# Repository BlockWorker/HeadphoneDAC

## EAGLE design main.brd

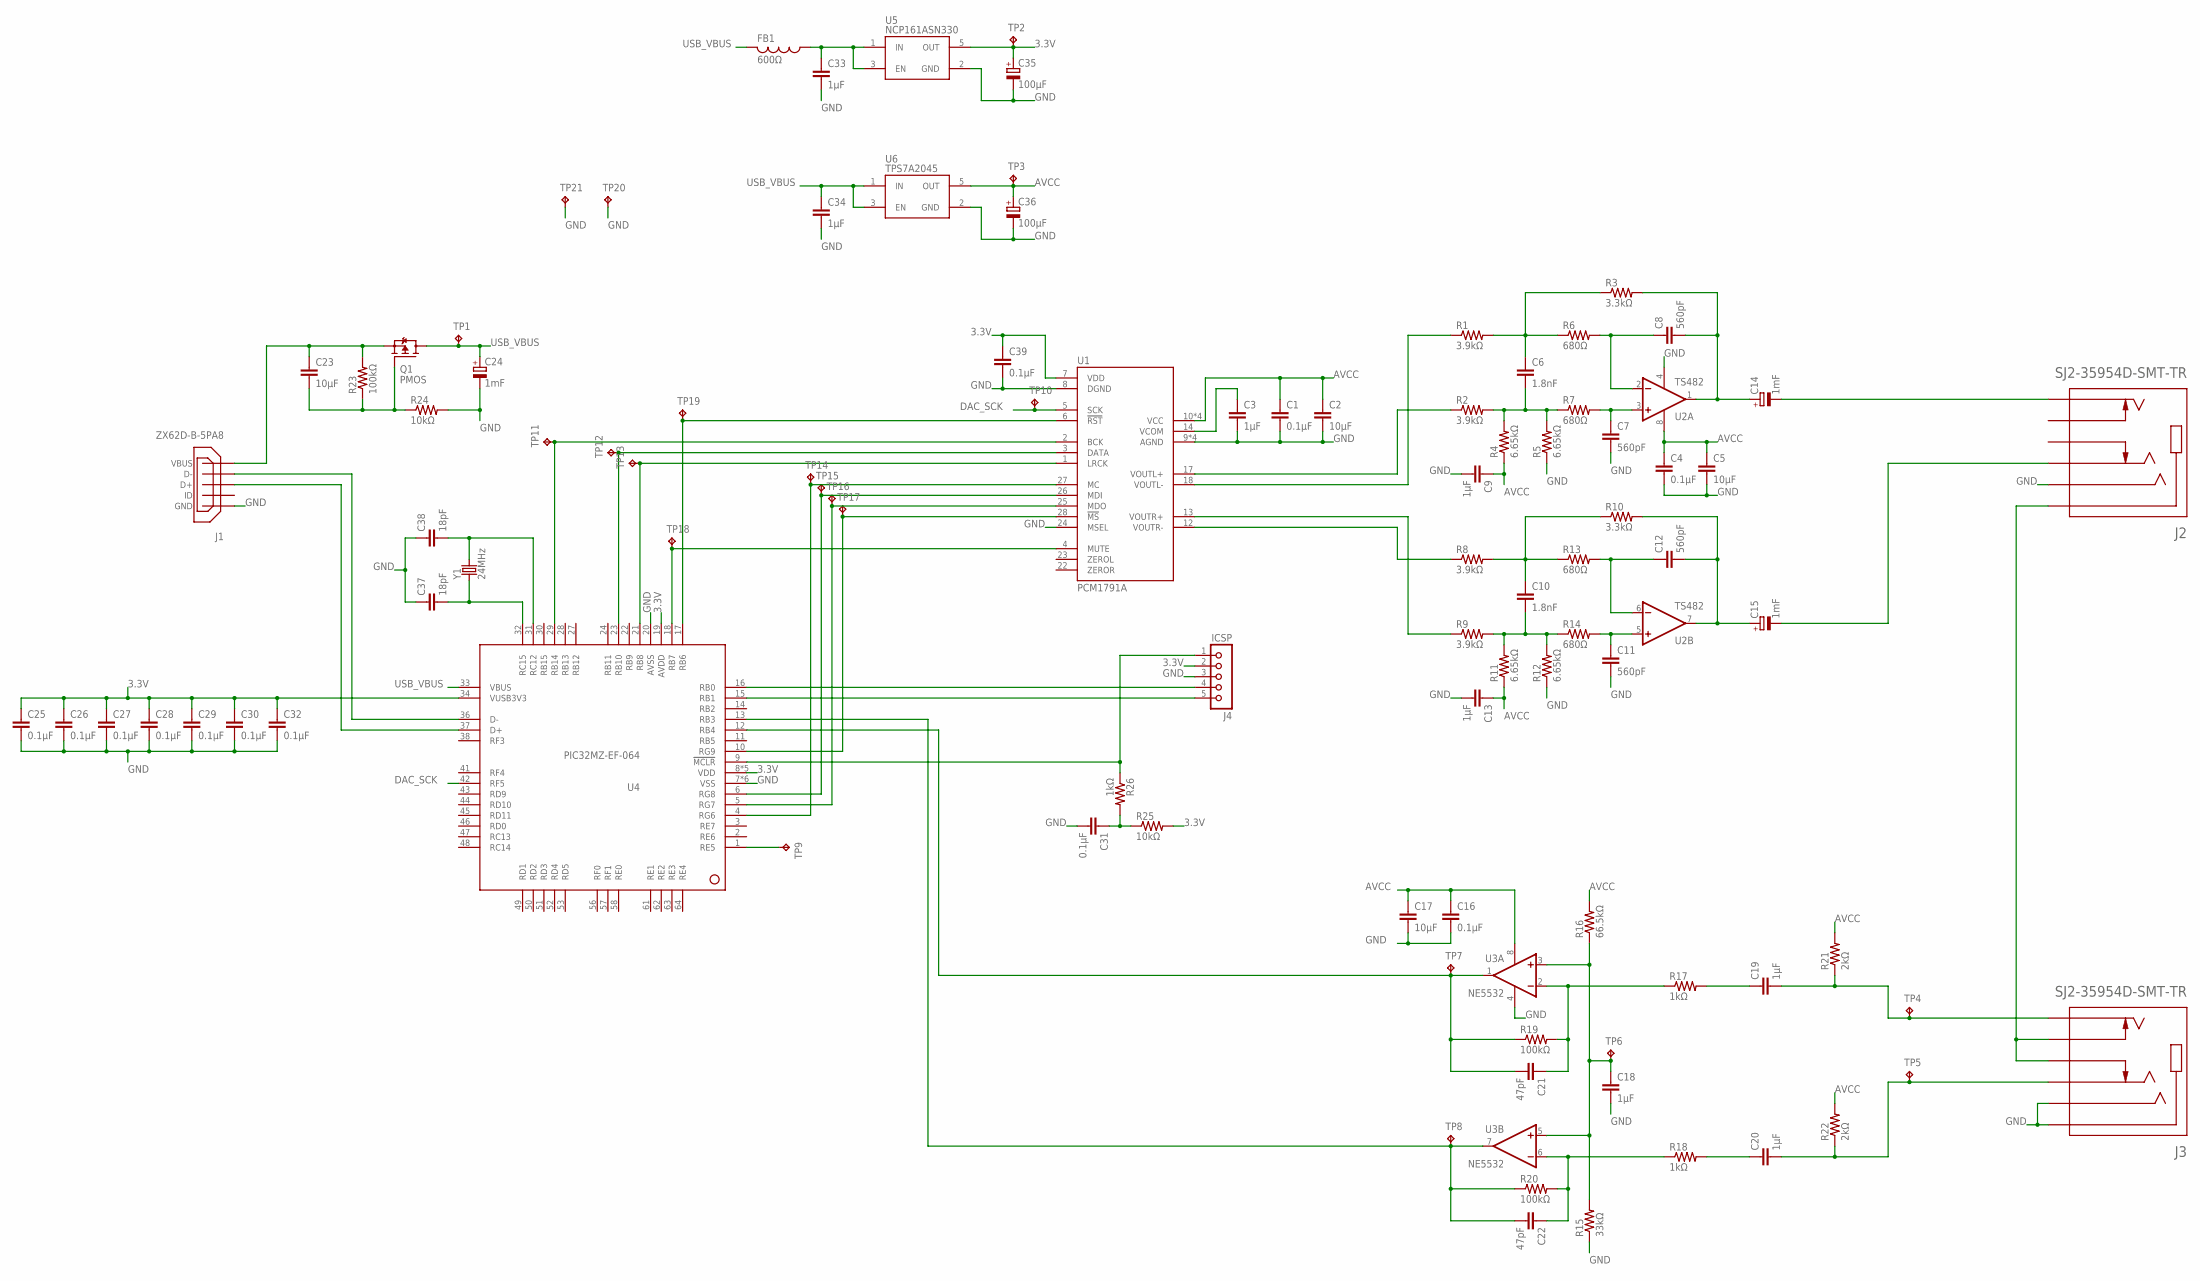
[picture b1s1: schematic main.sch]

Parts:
C1, C4, C16, C25, C26, C27, C28, C29, C30, C31, C32, C39: 0.1µF; C0603
C2, C5, C17, C23: 10µF; C0805
C3, C9, C13, C18, C33, C34: 1µF; C0805
C6, C10: 1.8nF; C0603
C7, C8, C11, C12: 560pF; C0603
C14, C15, C24: 1mF; E3,5-8-16-HORZ
C19, C20: 1µF; C050-050X075
C21, C22: 47pF; C050-045X075
C35, C36: 100µF; PANASONIC_D
C37, C38: 18pF; C0603
FB1: 600Ω; C0603
J1: ZX62D-B-5PA8
J2, J3: SJ2-35954D-SMT-TR; CUI_SJ2-35954D-SMT-TR
J4: ICSP; 5PIN-1.27
Q1: PMOS; SOT23
R1, R2, R8, R9: 3.9kΩ; R0603
R3, R10: 3.3kΩ; R0603
R4, R5, R11, R12: 6.65kΩ; R0603
R6, R7, R13, R14: 680Ω; R0603
R15: 33kΩ; R0603
R16: 66.5kΩ; R0603
R17, R18, R26: 1kΩ; R0603
R19, R20, R23: 100kΩ; R0603
R21, R22: 2kΩ; R0603
R24, R25: 10kΩ; R0603
TP1, TP2, TP3, TP4, TP5, TP6, TP7, TP8, TP9, TP10, TP11, TP12, TP13, TP14, TP15, TP16, TP17, TP18, TP19, TP20, TP21: RCU-0(J); TP_0603_JOINED
U1: PCM1791A; SSOP28
U2: TS482; MSOP8
U3: NE5532; SOIC8
U4: PIC32MZ-EF-064; TQFP64-10X10X1MM
U5: NCP161ASN330; SOT23-5L
U6: TPS7A2045; SOT23-5L
Y1: 24MHz; HC49/4HSMX

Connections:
3.3V: C25.1, C26.1, C27.1, C28.1, C29.1, C30.1, C32.1, C35.+, C39.1, J4.2, R25.2, TP2.1, U1.7 (VDD), U4.8 (VDD), U4.19 (AVDD), U4.26 (VDD), U4.34 (VUSB3V3), U4.39 (VDD), U4.54 (VDD), U4.60 (VDD), U5.5 (OUT)
3V3REG_IN: C33.1, FB1.1, U5.1 (IN), U5.3 (EN)
!MCLR: J4.1, R26.1, U4.9 (!MCLR)
!MCLR!_FILTER: C31.1, R25.1, R26.2
AMP_L_+: C7.1, R7.2, U2.3 (+IN)
AMP_L_-: C8.1, R6.2, U2.2 (-IN)
AMP_L_OUT: C8.2, C14.+, R3.2, U2.1 (OUT)
AMP_L_SUM_+: C6.2, R2.2, R4.2, R5.2, R7.1
AMP_L_SUM_-: C6.1, R1.2, R3.1, R6.1
AMP_R_+: C11.1, R14.2, U2.5 (+IN)
AMP_R_-: C12.1, R13.2, U2.6 (-IN)
AMP_R_OUT: C12.2, C15.+, R10.2, U2.7 (OUT)
AMP_R_SUM_+: C10.2, R9.2, R11.2, R12.2, R14.1
AMP_R_SUM_-: C10.1, R8.2, R10.1, R13.1
AVCC: C1.1, C2.1, C4.1, C5.1, C9.1, C13.1, C16.1, C17.1, C36.+, R4.1, R11.1, R16.2, R21.2, R22.2, TP3.1, U1.10 (VCC), U1.15 (VCC), U1.20 (VCC), U1.21 (VCC), U2.8 (V+), U3.8 (V+), U6.5 (OUT)
DAC_!MS: TP17.1, U1.28 (!MS), U4.10 (RG9)
DAC_!RST: TP19.1, U1.6 (!RST), U4.17 (RB6)
DAC_BCK: TP11.1, U1.2 (BCK), U4.29 (RB14)
DAC_DATA: TP12.1, U1.3 (DATA), U4.23 (RB10)
DAC_LRCK: TP13.1, U1.1 (LRCK), U4.21 (RB8)
DAC_MC: TP14.1, U1.27 (MC), U4.4 (RG6)
DAC_MISO: TP16.1, U1.25 (MDO), U4.5 (RG7)
DAC_MOSI: TP15.1, U1.26 (MDI), U4.6 (RG8)
DAC_MUTE: TP18.1, U1.4 (MUTE), U4.18 (RB7)
DAC_SCK: TP10.1, U1.5 (SCK), U4.42 (RF5)
DAC_VCOM: C3.1, U1.14 (VCOM)
DAC_VOUTL+: R2.1, U1.17 (VOUTL+)
DAC_VOUTL-: R1.1, U1.18 (VOUTL-)
DAC_VOUTR+: R9.1, U1.13 (VOUTR+)
DAC_VOUTR-: R8.1, U1.12 (VOUTR-)
DEBUG_UART: TP9.1, U4.1 (RE5)
GND: C1.2, C2.2, C3.2, C4.2, C5.2, C7.2, C9.2, C11.2, C13.2, C16.2, C17.2, C18.2, C24.-, C25.2, C26.2, C27.2, C28.2, C29.2, C30.2, C31.2, C32.2, C33.2, C34.2, C35.-, C36.-, C37.1, C38.1, C39.2, J1.5 (GND), J1.S1 (GND), J1.S2 (GND), J1.S3 (GND), J1.S4 (GND), J2.4 (RING2), J3.1 (SLEEVE), J3.4 (RING2), J4.3, R5.1, R12.1, R15.1, R24.2, TP20.1, TP21.1, U1.8 (DGND), U1.9 (AGND), U1.11 (AGND), U1.16 (AGND), U1.19 (AGND), U1.24 (MSEL), U2.4 (V-), U3.4 (V-), U4.7 (VSS), U4.20 (AVSS), U4.25 (VSS), U4.35 (VSS), U4.40 (VSS), U4.55 (VSS), U4.59 (VSS), U5.2 (GND), U6.2 (GND)
HP_L: C14.-, J2.2 (TIP)
HP_R: C15.-, J2.3 (RING1)
MIC_ALT: J2.1 (SLEEVE), J3.10 (TIP_SWITCH), J3.11 (RING1_SWITCH)
MIC_AMP_BIAS: C18.1, R15.2, R16.1, TP6.1, U3.3 (+IN), U3.5 (+IN)
MIC_L: C19.2, J3.2 (TIP), R21.1, TP4.1
MIC_L_AMPIN: C21.1, R17.1, R19.2, U3.2 (-IN)
MIC_L_AMPOUT: C21.2, R19.1, TP7.1, U3.1 (OUT), U4.12 (RB4)
MIC_L_COUPLED: C19.1, R17.2
MIC_R: C20.2, J3.3 (RING1), R22.1, TP5.1
MIC_R_AMPIN: C22.1, R18.1, R20.2, U3.6 (-IN)
MIC_R_AMPOUT: C22.2, R20.1, TP8.1, U3.7 (OUT), U4.13 (RB3)
MIC_R_COUPLED: C20.1, R18.2
OSC1: C38.2, U4.31 (RC12), Y1.2
OSC2: C37.2, U4.32 (RC15), Y1.1
PGEC: J4.5, U4.15 (RB1)
PGED: J4.4, U4.16 (RB0)
USB_D+: J1.3 (D+), U4.37 (D+)
USB_D-: J1.2 (D-), U4.36 (D-)
USB_VBUS: C24.+, C34.1, FB1.2, Q1.3 (D), TP1.1, U4.33 (VBUS), U6.1 (IN), U6.3 (EN)
USB_VBUS_RAMP: C23.2, Q1.1 (G), R23.1, R24.1
USB_VBUS_RAW: C23.1, J1.1 (VBUS), Q1.2 (S), R23.2

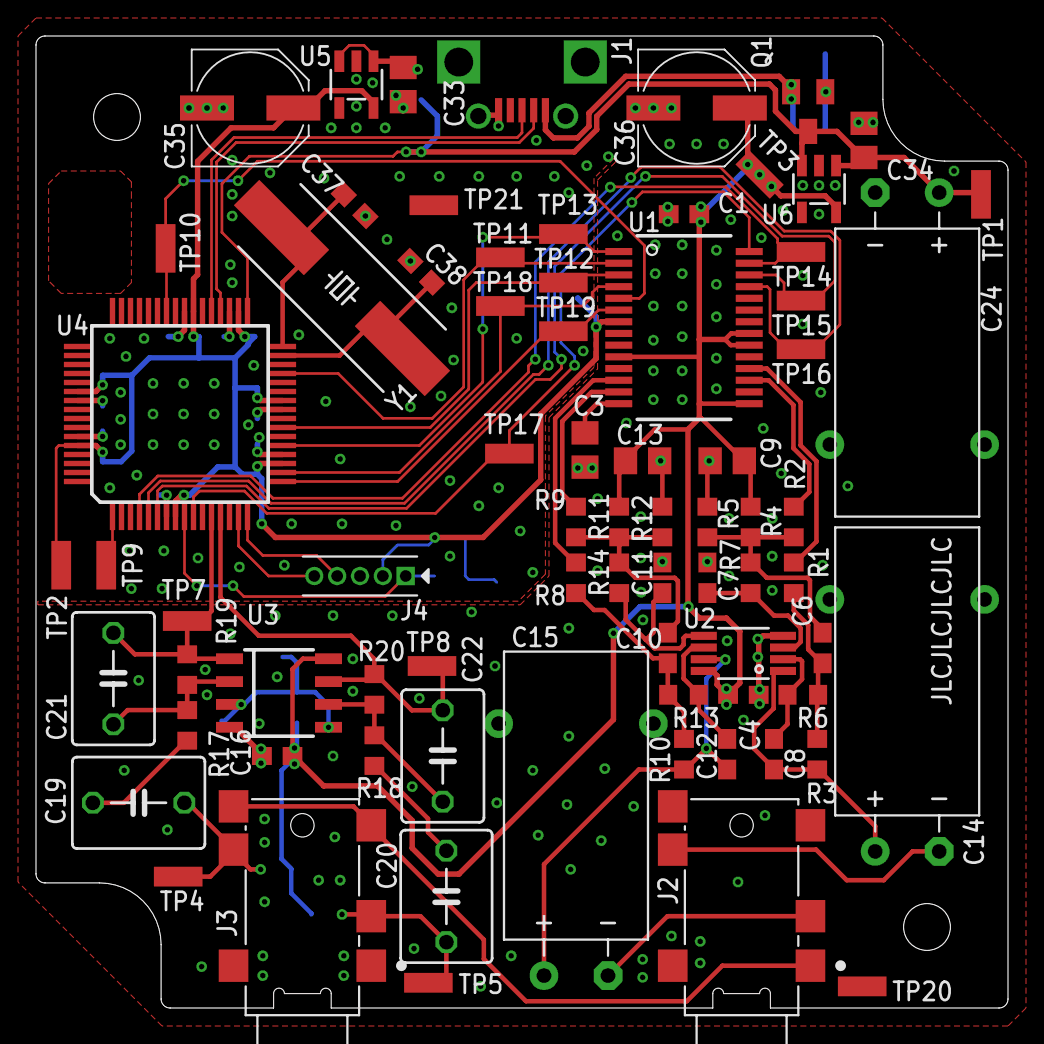
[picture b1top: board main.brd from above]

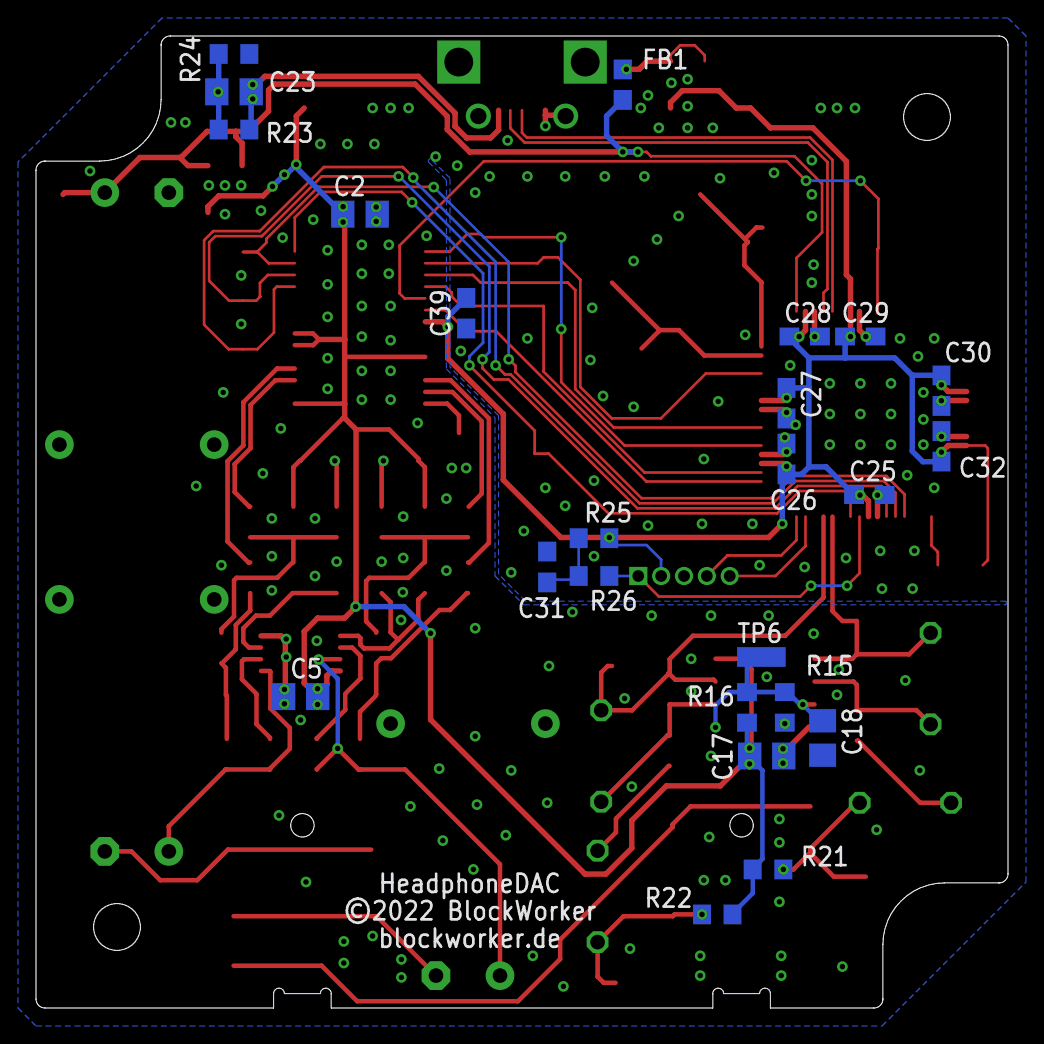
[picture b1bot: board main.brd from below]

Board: 2 copper layers, 54.0 x 54.0 mm, 99 parts (24 on the bottom side), 53 nets.

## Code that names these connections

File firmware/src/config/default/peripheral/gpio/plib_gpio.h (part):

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// *****************************************************************************


/*** Macros for MIC_L pin ***/
#define MIC_L_Get()               ((PORTB >> 4) & 0x1U)
#define MIC_L_PIN                  GPIO_PIN_RB4

/*** Macros for MIC_R pin ***/
#define MIC_R_Get()               ((PORTB >> 3) & 0x1U)
#define MIC_R_PIN                  GPIO_PIN_RB3

/*** Macros for PGEC pin ***/
#define PGEC_Set()               (LATBSET = (1U<<1))
#define PGEC_Clear()             (LATBCLR = (1U<<1))
#define PGEC_Toggle()            (LATBINV= (1U<<1))
#define PGEC_OutputEnable()      (TRISBCLR = (1U<<1))
#define PGEC_InputEnable()       (TRISBSET = (1U<<1))
#define PGEC_Get()               ((PORTB >> 1) & 0x1U)
#define PGEC_PIN                  GPIO_PIN_RB1

/*** Macros for PGED pin ***/
#define PGED_Set()               (LATBSET = (1U<<0))
#define PGED_Clear()             (LATBCLR = (1U<<0))
#define PGED_Toggle()            (LATBINV= (1U<<0))
#define PGED_OutputEnable()      (TRISBCLR = (1U<<0))
#define PGED_InputEnable()       (TRISBSET = (1U<<0))
#define PGED_Get()               ((PORTB >> 0) & 0x1U)
#define PGED_PIN                  GPIO_PIN_RB0

/*** Macros for DAC_RST_N pin ***/
#define DAC_RST_N_Set()               (LATBSET = (1U<<6))
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
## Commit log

2022-11-14 Progress, no audio transfers yet

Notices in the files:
firmware/src/config/default/peripheral/gpio/plib_gpio.h:
Copyright (C) 2019 Microchip Technology Inc. and its subsidiaries.
main.brd:
©2022 BlockWorker
